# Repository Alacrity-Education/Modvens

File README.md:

# Modvens
Inspired by IKEA’s Frekvens, this project turns individual LED matrix cubes into building blocks. You can combine them into a custom-sized display for scrolling text, animations and data visualizations.

## Hardware

Each cube has two boards connected by a 15-pin flat flex cable:
- **Interface board** – soldered to the back of the Frekvens LED matrix; adapts its pads to the FFC connector and filters the LED supply.
- **Main board** – sits inside the cube and drives the matrix *(in progress)*.

### Interface board

A small adapter board (32 × 48.5 mm) that attaches to the back of the original Frekvens LED matrix PCB and breaks its signals out to a flat flex cable. The cable connects to the main board inside the cube.

The KiCad project lives in [`CAD/modvens/`](CAD/modvens/).

#### Front side (F.Cu) – matrix interface

The custom footprint `Project_Components:frekvens` (U1) mirrors the row of pads on the edge of the Frekvens LED matrix PCB, so the two boards can be soldered pad-to-pad. The pad positions and spacing come from measurements of the original board:

| Pin | Signal | Notes |
|-----|--------|-------|
| 1 | GND | |
| 2 | Latch | |
| 3 | Clk | |
| 4 | DA | Serial data |
| 5 | EN | Output enable |
| 6 | VCC | Fed from the filtered `VLED` rail |
| 7 | MIC | |
| 8 | CH6 | Not connected |

#### Back side (B.Cu) – connector and power filter

- **J1 – GCT FFC3A20-15-G**, a 15-pin flat flex connector carrying the matrix signals and power:

  | J1 pin | Signal |
  |--------|--------|
  | 1, 3, 5, 7, 9, 11, 12 | GND |
  | 2 | MIC |
  | 4 | EN |
  | 6 | Latch |
  | 8 | Clk |
  | 10 | DA |
  | 13, 14, 15 | +4V |

  Each signal sits between ground pins to reduce crosstalk along the cable.

- **LC filter** between the incoming `+4V` supply and the `VLED` rail that powers the matrix:
  - Input (`+4V`): 100 µF electrolytic (C12), 2 × 10 µF 1812 (C13, C14), 10 µF 0603 (C15)
  - Series inductor: 10 µH TaiTech TMPC1265 (L1)
  - Output (`VLED`): 3 × 1000 µF electrolytic (C9–C11), 4 × 10 µF 1812 (C5–C8), 4 × 10 µF 0603 (C1–C4)

  The bulk capacitance on `VLED` buffers the large current spikes from the multiplexed LEDs, and the inductor keeps them from going back onto the shared supply.

## Status

- [x] Interface board design
- [ ] Main board design
- [ ] Send boards to manufacturing
- [ ] Assembly
- [ ] Write the firmware
- [ ] Test the firmware on the boards

## References

- [hlord2000/nordic-lib-kicad](https://github.com/hlord2000/nordic-lib-kicad) – KiCad library for Nordic Semiconductor parts

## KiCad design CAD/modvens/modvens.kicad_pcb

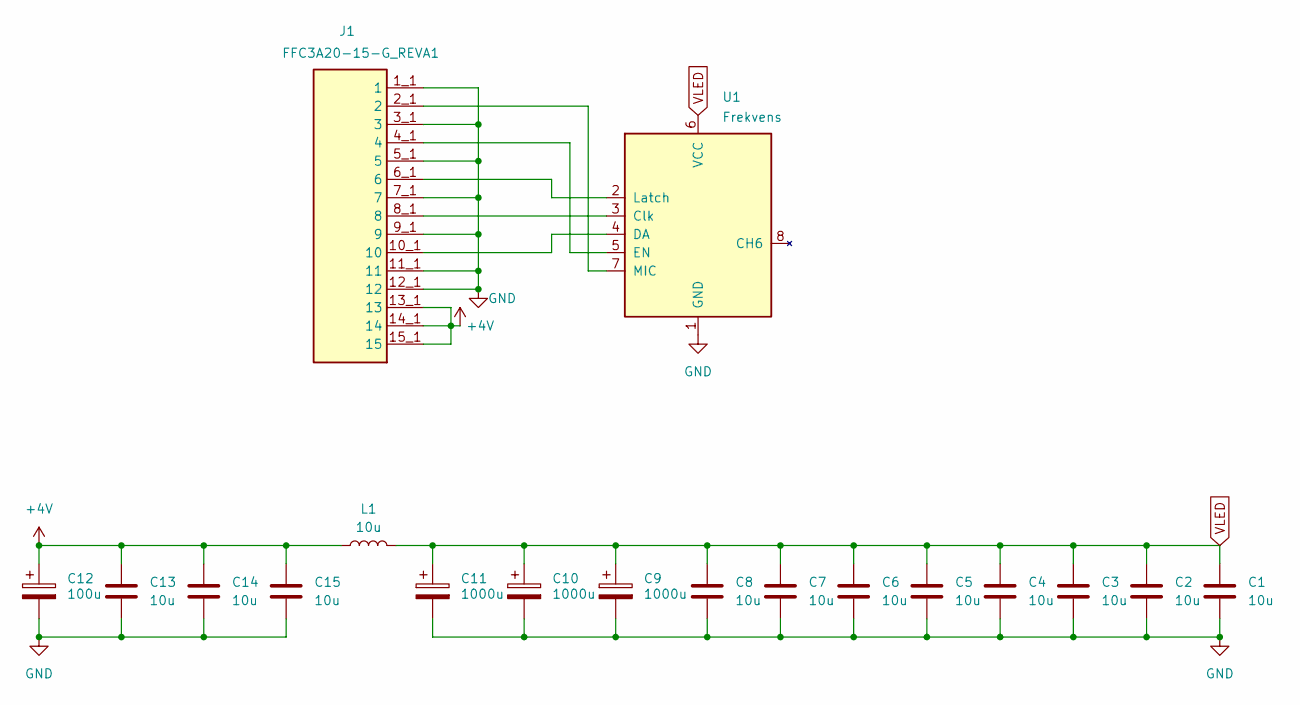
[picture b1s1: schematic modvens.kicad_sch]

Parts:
C1, C2, C3, C4, C15: 10u; C_0603_1608Metric; LCSC C1691
C5, C6, C7, C8, C13, C14: 10u; C_1812_4532Metric; LCSC C1021609
C9, C10, C11: 1000u; CP_Elec_10x10.5; LCSC C278397
C12: 100u; C_Elec_6.3x5.8; LCSC C128532
J1: FFC3A20-15-G_REVA1; GCT_FFC3A20-15-G_REVA1; MPN FFC3A20-15-G
L1: 10u; L_TaiTech_TMPC1265_13.5x12.5mm; LCSC C840531
U1: Frekvens; frekvens

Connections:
+4V: C12.1, C13.1, C14.1, C15.1, J1.13_1 (13), J1.13_2 (13), J1.14_1 (14), J1.14_2 (14), J1.15_1 (15), J1.15_2 (15), L1.1
GND: C1.2, C2.2, C3.2, C4.2, C5.2, C6.2, C7.2, C8.2, C9.2, C10.2, C11.2, C12.2, C13.2, C14.2, C15.2, J1.1_1 (1), J1.1_2 (1), J1.3_1 (3), J1.3_2 (3), J1.5_1 (5), J1.5_2 (5), J1.7_1 (7), J1.7_2 (7), J1.9_1 (9), J1.9_2 (9), J1.11_1 (11), J1.11_2 (11), J1.12_1 (12), J1.12_2 (12), U1.1 (GND)
unnamed: J1.8_1 (8), J1.8_2 (8), U1.3 (Clk)
unnamed: J1.10_1 (10), J1.10_2 (10), U1.4 (DA)
unnamed: J1.4_1 (4), J1.4_2 (4), U1.5 (EN)
unnamed: J1.6_1 (6), J1.6_2 (6), U1.2 (Latch)
unnamed: J1.2_1 (2), J1.2_2 (2), U1.7 (MIC)
VLED: C1.1, C2.1, C3.1, C4.1, C5.1, C6.1, C7.1, C8.1, C9.1, C10.1, C11.1, L1.2, U1.6 (VCC)

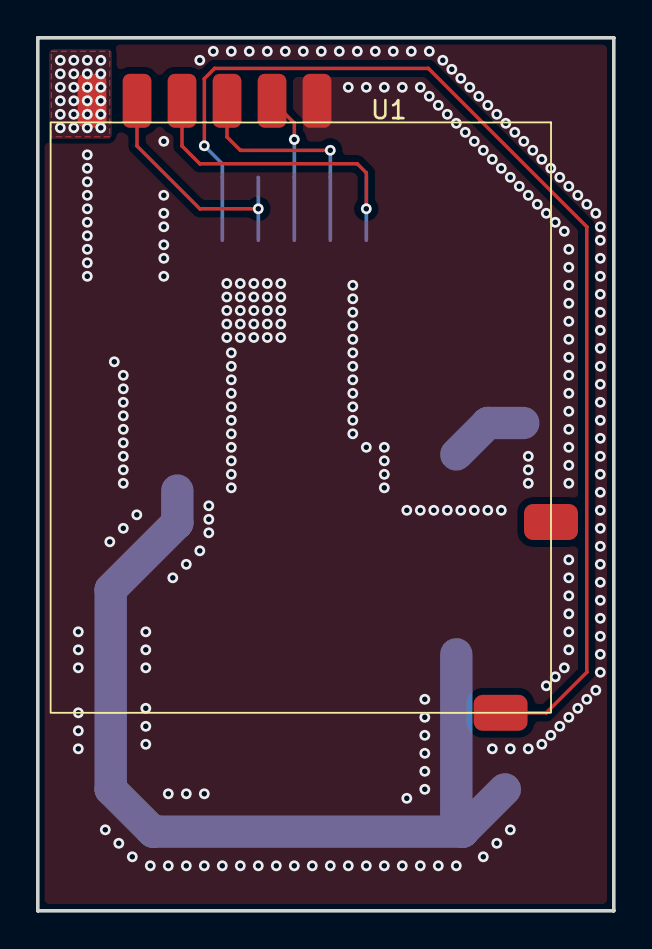
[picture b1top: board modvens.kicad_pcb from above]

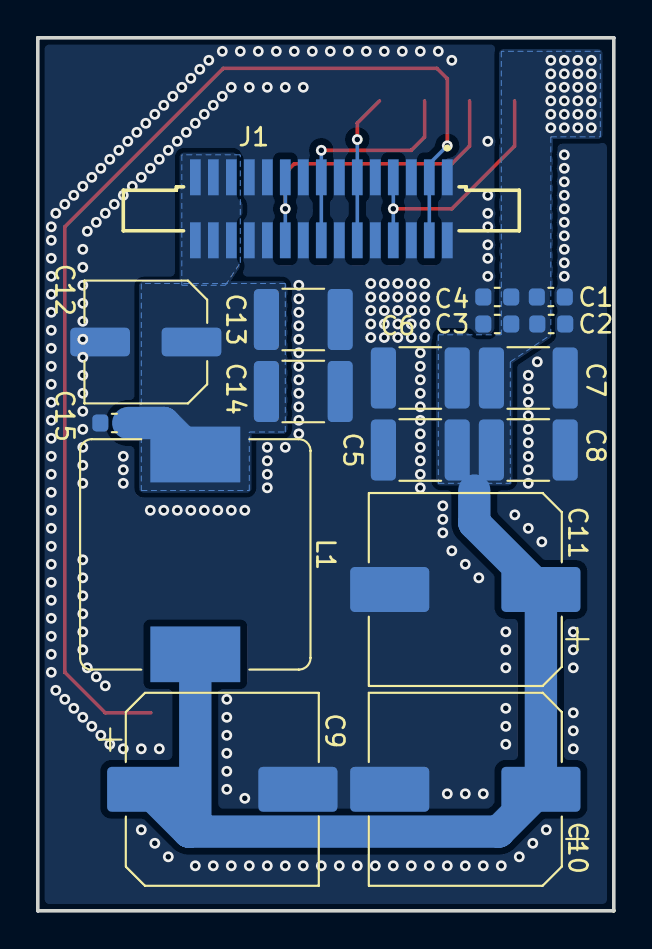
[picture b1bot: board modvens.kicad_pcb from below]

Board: 2 copper layers, 32.0 x 48.5 mm, 18 parts (17 on the bottom side), 8 nets.
